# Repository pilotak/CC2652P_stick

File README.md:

# CC2652P USB stick
CC2652P based Zigbee coordinator/router

## Flashing
- download [cc2538-bsl](https://github.com/JelmerT/cc2538-bsl) (you may need to install Python and/or other dependecies listed there)
- download [firmware](https://github.com/Koenkk/Z-Stack-firmware)
- run (change COM port to suit yours and specify location of downloaded FW)
```
python cc2538-bsl.py -p COM8 -w ./CC1352P2_CC2652P_other_router_20210128.hex
```

### BOM
| Qty | Value | Package | Component |
|:---:| --------- | ----- | ------- |
| 2 | 1uF/10V | 0805 | Ceramic capacitor |
| 1 | 100n | 0805 | Ceramic capacitor |
| 1 | 10n | 0805 | Ceramic capacitor |
| 1 | CH340C | SO16 | USB to Serial |
| 1 | USB A | | USB Connector |
| 1 | Red LED | 0603 | |
| 1 | Green LED | 0603 | |
| 1 | 100R | 0805 | Resistor |
| 1 | 1K | 0805 | Resistor |
| 1 | 820R | 0805 | Resistor |
| 1 | 10K | 0805 | Resistor |
| 1 | SMD button |  |  |
| 1 | MCP1802T-3302I/OT | SOT23-5 | LDO regulator |
| 1 | EBYTE-E72 |  | CC2652P based wireless module |
| 1 | 1551USB2 |  | USB enclosure by Hammond |

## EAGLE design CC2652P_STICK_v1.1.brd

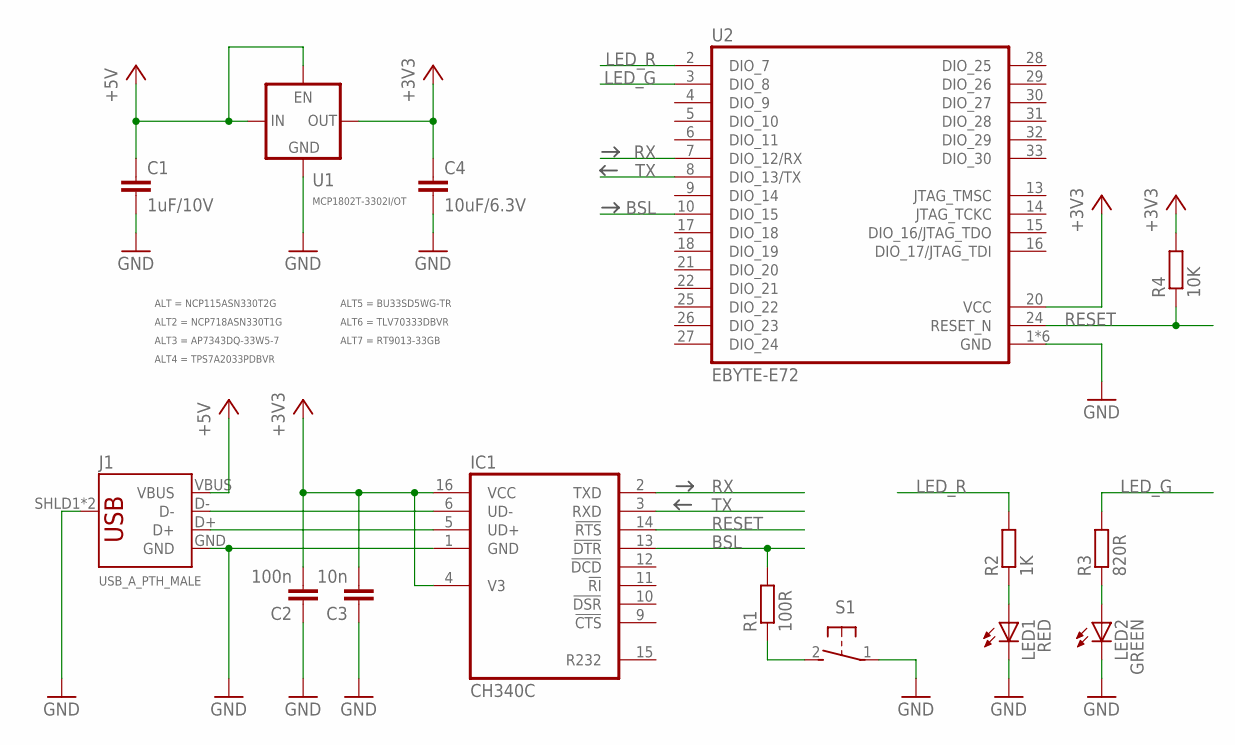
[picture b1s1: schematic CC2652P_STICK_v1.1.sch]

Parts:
C1: 1uF/10V; C0805
C2: 100n; C0805
C3: 10n; C0805
C4: 10uF/6.3V; C0805
IC1: CH340C; SO16
J1: USB_A_PTH_MALE; USB-A-H
LED1: RED; LED0603
LED2: GREEN; LED0603
R1: 100R; R0805
R2: 1K; R0805
R3: 820R; R0805
R4: 10K; R0805
S1: DTSM-3
U1: MCP1802T-3302I/OT; SOT23-5
U2: EBYTE-E72

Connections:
+3V3: C2.2, C3.2, C4.1, IC1.4 (V3), IC1.16 (VCC), R4.2, U1.5 (VOUT), U2.20 (VCC)
+5V: C1.1, J1.VBUS, U1.1 (VIN), U1.3 (EN)
BSL: IC1.13 (!DTR), R1.2, U2.10 (DIO_15)
DN: IC1.6 (UD-), J1.D-
DP: IC1.5 (UD+), J1.D+
GND: C1.2, C2.1, C3.1, C4.2, IC1.1 (GND), J1.GND, J1.SHLD1 (SHIELD), J1.SHLD2 (SHIELD), LED1.C, LED2.C, S1.1, U1.2 (GND), U2.1 (GND), U2.11 (GND), U2.12 (GND), U2.19 (GND), U2.23 (GND), U2.34 (GND)
LED_G: R3.2, U2.3 (DIO_8)
LED_R: R2.2, U2.2 (DIO_7)
unnamed: LED2.A, R3.1
unnamed: LED1.A, R2.1
unnamed: R1.1, S1.2
RESET: IC1.14 (!RTS), R4.1, U2.24 (RESET_N)
RX: IC1.2 (TXD), U2.7 (DIO_12/RX)
TX: IC1.3 (RXD), U2.8 (DIO_13/TX)

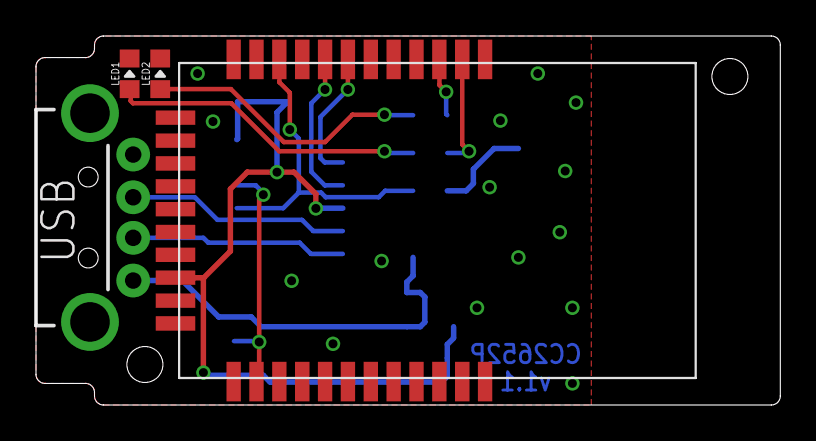
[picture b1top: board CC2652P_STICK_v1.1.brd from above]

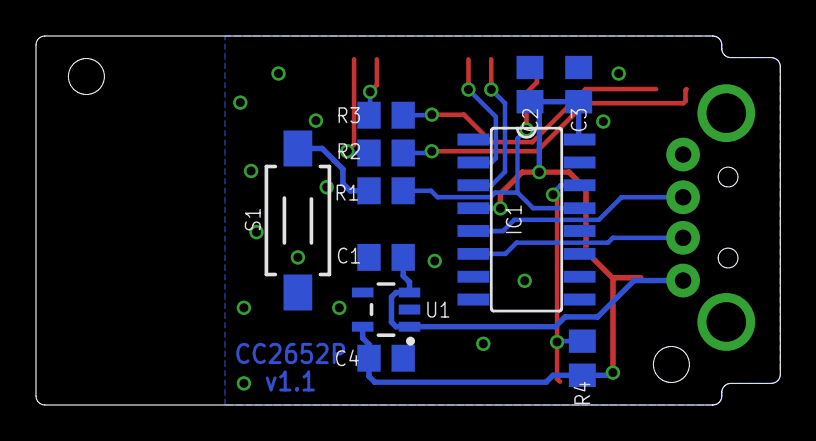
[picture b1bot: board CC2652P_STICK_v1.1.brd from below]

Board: 2 copper layers, 41.4 x 20.5 mm, 15 parts (11 on the bottom side), 14 nets.

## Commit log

2021-12-19 v1.1
2021-12-19 BOM update

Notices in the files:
parts and their libraries:
SparkFun-Connectors: Licensing: Creative Commons ShareAlike 4.0 International - https://creativecommons.org/licenses/by-sa/4.0
